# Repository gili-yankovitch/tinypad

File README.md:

# TinyPad
This is the TinyPad. A small USB Macro Pad based on the ATTiny85 with three buttons and uses the VUSB project to simulate the USB protocol.

## Prerequisits
### Software
Please install the following software to be able to flash software to the device:
* [Arduino SDK](https://www.arduino.cc/en/software)
* [Platformio](https://platformio.org/install/cli) or VScode with Platformio AddOn
* [Digispark Drivers](https://github.com/digistump/DigistumpArduino/releases/download/1.6.7/Digistump.Drivers.zip)

### Hardware
All PCB specs are provided here under hardware/ and this can be easily manufactured as well as paneled for a larger volume. There are no special requirements for this board's manufacturing process.

#### Bill of Materials
| Quantity | Component Description | Mfr. No | Datasheet |
|----------|-----------------------|---------|-----------|
| 2 | SMD 1/4W 68 Ohm 1% 0805  | RL1220S-680-F | [Datasheet](https://www.mouser.co.il/datasheet/2/392/n_catalog_partition08_en-1545266.pdf) |
| 4 | SMD 1 kOhms 125 mW 0805 5% | RC0805JR-071KL | [Datasheet](https://www.mouser.co.il/datasheet/2/447/PYu_RC_Group_51_RoHS_L_11-1984063.pdf) |
| 2 | DIODE, SMALL SIG, 300V, 0.15A, SOD-123F | 1N4148W+ | [Datasheet](https://admin.lion.co.il/api/documents?lion_sku=F5GHRC&file=0) |
| 3 | SMD/SMT 50V 0.1uF X7R 0805 10% | C0805C104K5RAC7411 | [Datasheet](https://www.mouser.co.il/datasheet/2/212/KEM_C1002_X7R_SMD-1102033.pdf) |
| 1 | MCU AVR 8K FLSH 512B EE 512B SRAM ADC 5V | ATTiny85-20SU | [Datasheet](https://www.mouser.co.il/datasheet/2/268/Atmel_2586_AVR_8_bit_Microcontroller_ATtiny25_ATti-1315542.pdf) |
| 1 | Type C 16Pins SMT Socket Connector USB 3.1 Type-C Female MD DIP | [Link](https://www.aliexpress.com/item/4001076043694.html?spm=a2g0o.order_list.0.0.2e2f1802zEBigU) | [Datasheet](https://ae01.alicdn.com/kf/H1e697b3dd3c54072b04ede95a2d44105H.jpg)
| 3 | 0.2W Intelligent external control surface mount SMD LED | SK6812Mini-E | [Datasheet](https://cdn-shop.adafruit.com/product-files/4960/4960_SK6812MINI-E_REV02_EN.pdf) |

# Software
## Software Building
Building the software is easy using platformio. Either run the [build.bat](build.bat) script, or simply execute:
```
pio run --environment attiny85
```

### Software Flashing Using Arduino as an ISP using the broken-out pins
The [platformio.ini](platformio.ini) project is currently configured to be flashed using the Digispark bootloader, but it can also be flashed directly using an Arduino as an ISP. Simply connect the Arduino to the broken-out pin headers, uncomment the commented lines under platforio.ini and run:
```
pio run -t fuses
pio run --environment attiny85 --target upload
```

### Software Flashing Using the Digispark bootloader using the USB port
Flashing software using the USB port would require flashing the ATTiny85 with the bootloader [Attiny85.hex](Digistump/bootloader/ATtiny85.hex) using the flash script [Burn_AT85_bootloader.bat](Digistump/bootloader/Burn_AT85_bootloader.bat) which also sets the appropriate fuses at flash time.
```
<ArduinoFolder>\packages\arduino\tools\avrdude\6.3.0-arduino17\bin\avrdude.exe -C"<ArduinoFolder>\packages\arduino\tools\avrdude\6.3.0-arduino17\etc\avrdude.conf" -v -pattiny85 -cstk500v1 -P<COMPORT> -b19200 -Uflash:w:"ATtiny85.hex":i -U lfuse:w:0xe1:m -U hfuse:w:0xdd:m -U efuse:w:0xfe:m
```
* Don't forget to swap `<ArduinoFolder>` and `<COMPORT>` to the appropriate arduino install folder and the Arduino COM port.

After that, you can build the software normally and flash it using the USB port. Run the following command and remember to only plug in the USB once the flash utility indicates it:
```
pio run --environment attiny85 --target upload
```

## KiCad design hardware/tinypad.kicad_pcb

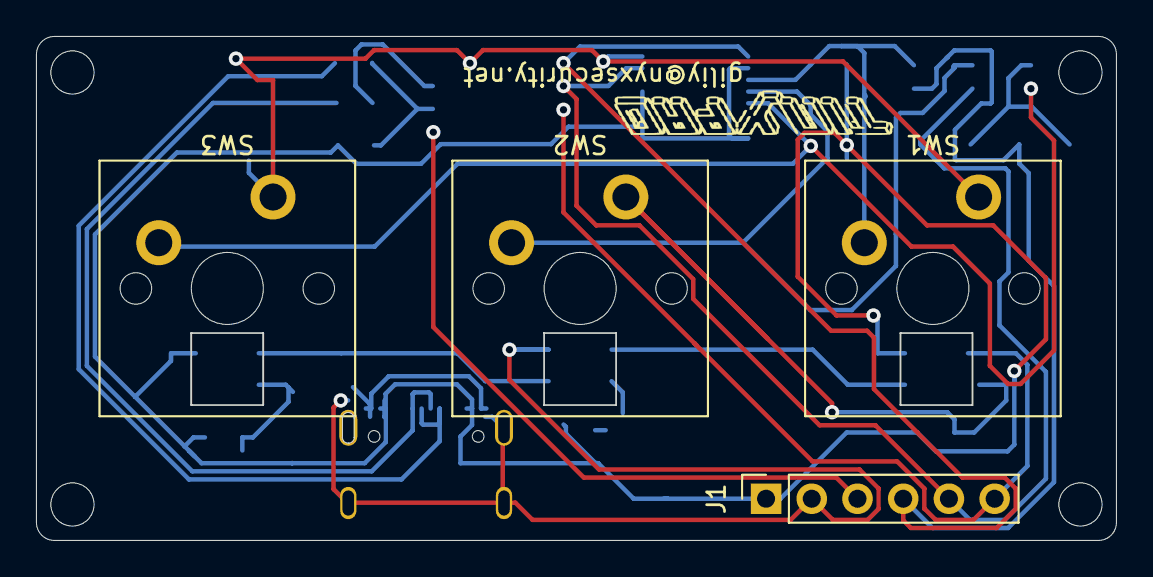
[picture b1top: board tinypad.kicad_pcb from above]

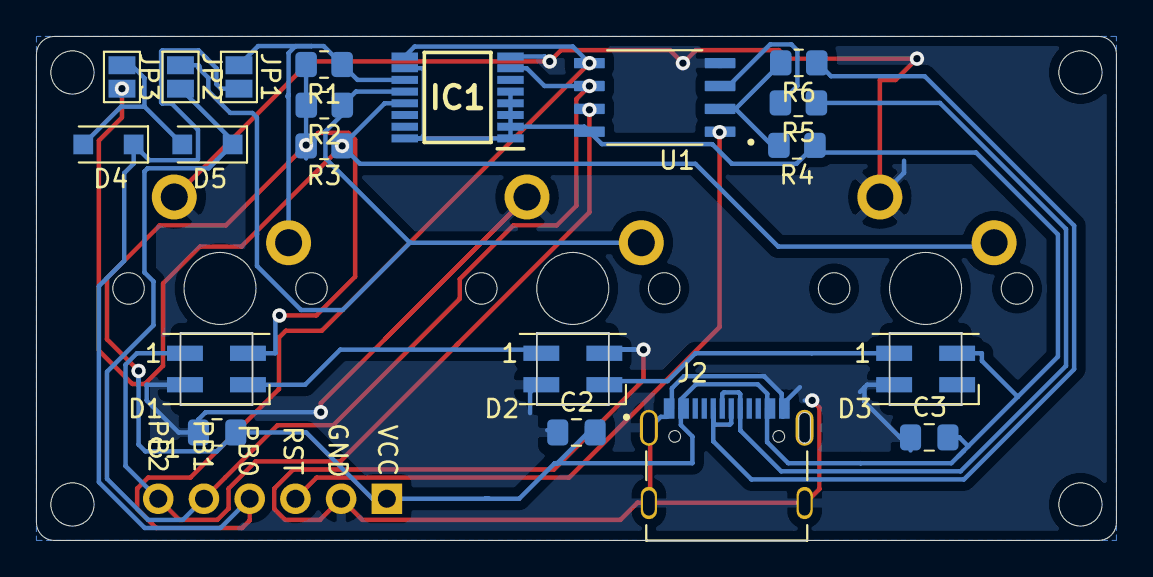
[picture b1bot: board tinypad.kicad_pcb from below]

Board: 2 copper layers, 60.0 x 27.9 mm, 24 parts (20 on the bottom side), 16 nets.

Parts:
C1, C2, C3: 0.1uF; C_0805_2012Metric_Pad1.18x1.45mm_HandSolder
D1, D2, D3: SK6812MINI; LED_SK6812MINI_PLCC4_3.5x3.5mm_P1.75mm
D4, D5: DIODE; D_SOD-123F
IC1: CD74HC147PWR; SOP65P640X120-16N
J1: Conn_01x06_Female; PinSocket_1x06_P2.54mm_Vertical
J2: CSP-USC16-TR; VALCON_CSP-USC16-TR-Fixed
JP1, JP2, JP3: SolderJumper_2_Open; SolderJumper-2_P1.3mm_Open_Pad1.0x1.5mm
R1, R2, R3: 1k; R_0805_2012Metric_Pad1.20x1.40mm_HandSolder
R4: 1.5k; R_0805_2012Metric_Pad1.20x1.40mm_HandSolder
R5, R6: 68R; R_0805_2012Metric_Pad1.20x1.40mm_HandSolder
SW1, SW2, SW3: SW_Push; SW_Cherry_MX_PCB_1.00u
U1: ATtiny85-20SU; SOIC127P798X216-8N

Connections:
BTN1: IC1.11, JP1.1, R1.1, SW1.1
BTN2: IC1.12, JP2.1, R2.1, SW2.1
BTN3: IC1.13, JP3.1, R3.1, SW3.1
D+: R5.2, U1.3
D-: R4.2, R6.2, U1.2
GND: C1.2, C2.2, C3.2, D1.2, D2.2, D3.2, IC1.8, J1.2, J2.A1, J2.A12, J2.B1, J2.B12, J2.S1, J2.S2, J2.S3, J2.S4, SW1.2, SW2.2, SW3.2, U1.4
unnamed: D1.1, D2.3
unnamed: D2.1, D3.3
unnamed: D4.2, D5.2, JP3.2
unnamed: J2.A6, J2.B6, R5.1
unnamed: J2.A7, J2.B7, R6.1
PB0: D4.1, IC1.9, J1.4, JP1.2, U1.5
PB1: D5.1, IC1.7, J1.5, JP2.2, U1.6
PB2: D1.3, J1.6, U1.7
RST: J1.3, U1.1
VCC: C1.1, C2.1, C3.1, D1.4, D2.4, D3.4, IC1.1, IC1.2, IC1.3, IC1.4, IC1.5, IC1.10, IC1.16, J1.1, J2.A4, J2.A9, J2.B4, J2.B9, R1.2, R2.2, R3.2, R4.1, U1.8

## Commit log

2022-10-14 Fixing clock source permanently and adding cmdline platformio build + upload
2022-10-15 Adding hardware schematics to repo
2022-10-15 Removing zip file of repo
2022-10-15 Reorganizing files
2022-10-15 Removing duplicate files
2022-10-15 Fixing paths in flash script
2022-10-15 Fixing back image
2022-10-15 Update README.md
    Initial README documentation
2022-10-15 Fixing minor wiring issues
